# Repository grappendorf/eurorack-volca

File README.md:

Eurorack Volca
==============

If you like [Korg Volcas](http://www.korg.com/de/products/dj/volca_beats/) and
you've got a [Eurorack system](https://en.wikipedia.org/wiki/Doepfer_A-100), you can combine them
with this simple 3D printable Eurorack panel (40 HP).

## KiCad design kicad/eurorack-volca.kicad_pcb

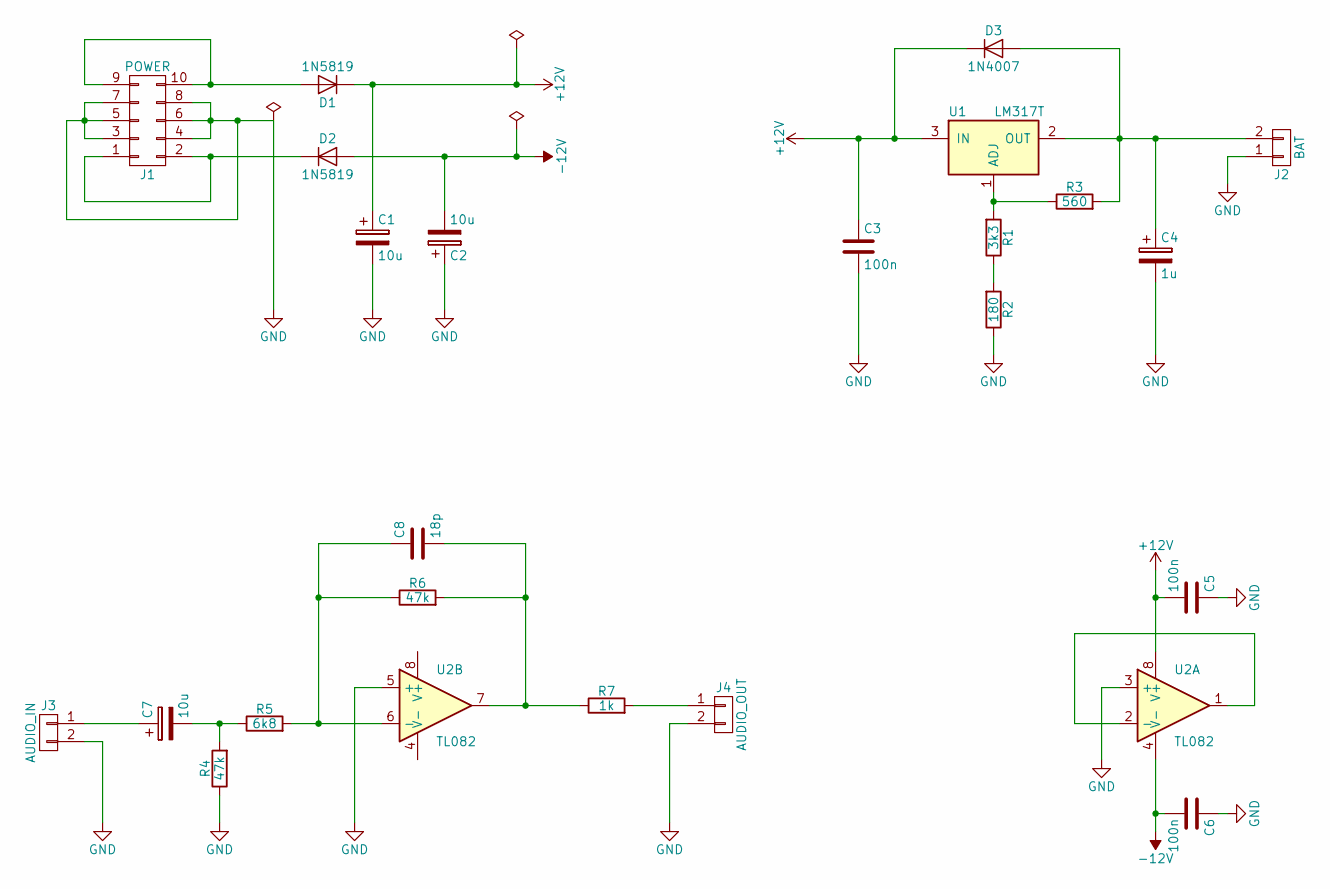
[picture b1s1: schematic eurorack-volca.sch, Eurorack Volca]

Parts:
C1, C2, C7: 10u; CP_Radial_D6.3mm_P2.50mm
C3, C5, C6: 100n; C_Disc_D5.0mm_W2.5mm_P2.50mm
C4: 1u; CP_Radial_D6.3mm_P2.50mm
C8: 18p; C_Disc_D5.0mm_W2.5mm_P2.50mm
D1, D2: 1N5819; D_DO-41_SOD81_P7.62mm_Horizontal
D3: 1N4007; D_DO-41_SOD81_P7.62mm_Horizontal
J1: POWER; vasch_strip_5x2
J2: BAT; Pin_Header_Angled_1x02_Pitch2.54mm
J3: AUDIO_IN; Pin_Header_Angled_1x02_Pitch2.54mm
J4: AUDIO_OUT; Pin_Header_Angled_1x02_Pitch2.54mm
R1: 3k3; R_Axial_DIN0204_L3.6mm_D1.6mm_P7.62mm_Horizontal
R2: 180; R_Axial_DIN0204_L3.6mm_D1.6mm_P7.62mm_Horizontal
R3: 560; R_Axial_DIN0204_L3.6mm_D1.6mm_P7.62mm_Horizontal
R4, R6: 47k; R_Axial_DIN0204_L3.6mm_D1.6mm_P7.62mm_Horizontal
R5: 6k8; R_Axial_DIN0204_L3.6mm_D1.6mm_P7.62mm_Horizontal
R7: 1k; R_Axial_DIN0204_L3.6mm_D1.6mm_P7.62mm_Horizontal
U1: LM317T; TO-220-3_Horizontal
U2: TL082; DIP-8_W7.62mm_Socket_LongPads

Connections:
+12V: C1.1, C3.1, C5.2, D1.1 (K), D3.1 (K), U1.3 (IN), U2.8 (V+)
-12V: C2.2, C6.2, D2.2 (A), U2.4 (V-)
GND: C1.2, C2.1, C3.2, C4.2, C5.1, C6.1, J1.3, J1.4, J1.5, J1.6, J1.7, J1.8, J2.1, J3.2, J4.2, R2.1, R4.1, U2.3 (+), U2.5 (+)
unnamed: C4.1, D3.2 (A), J2.2, R3.2, U1.2 (OUT)
unnamed: C7.1, J3.1
unnamed: C7.2, R4.2, R5.1
unnamed: C8.1, R5.2, R6.1, U2.6 (-)
unnamed: C8.2, R6.2, R7.1, U2.7
unnamed: D1.2 (A), J1.9, J1.10
unnamed: D2.1 (K), J1.1, J1.2
unnamed: J4.1, R7.2
unnamed: R1.1, R2.2
unnamed: R1.2, R3.1, U1.1 (ADJ)
unnamed: U2.1, U2.2 (-)

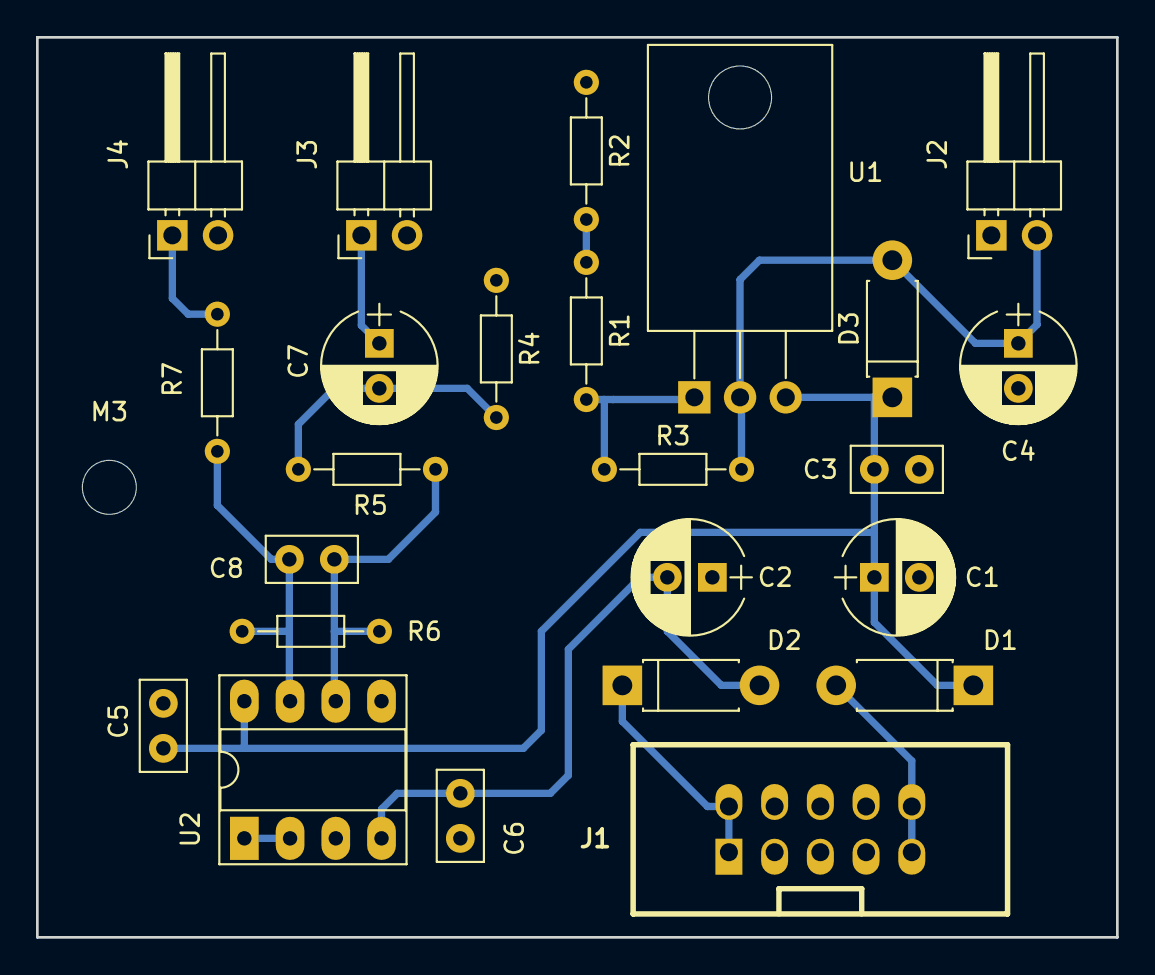
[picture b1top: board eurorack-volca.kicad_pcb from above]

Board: 2 copper layers, 60.0 x 50.0 mm, 25 parts (0 on the bottom side), 14 nets.

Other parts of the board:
M3: M3; MountingHole_3.2mm_M3

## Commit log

2017-11-23 root
2017-11-23 inital commit
